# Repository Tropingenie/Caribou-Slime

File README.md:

SlimeVR PCB using ESP32-C3 and BMI 270
## Methodology
This design is intended to be assembled either completely by hand, or with some PCBA and finished by hand. Component selection is built around this, prioritizing larger form factor SMT components where possible, to ensure compatibility with and minimizing cost of the PCBA, while maintaining relatively simple assembly when done by hand.
## BOM
|    Component    |            Choice            | Amount | Cost per | Cost with Shipping |                                                                           Quick Link                                                                                                            |
|:---------------:|:----------------------------:|:------:|:--------:|:------------------:|:----------------------------------------------------------------------------------------------------------------------------------------------------------------------------------------------------------------:|
| Microcontroller | ESP32-C3 Supermini Dev Board | 12     | $2.90    | ~$41               | [AliExpress](https://www.aliexpress.com/item/1005005877531694.html), [Datasheet](https://www.tindie.com/products/adz1122/esp32-c3-development-board-esp32-supermini/), [Schematic](https://s11.ax1x.com/2023/06/26/pCUheR1.png) |
| IMU             | BMI270                       | 12     | $1.75    | ~$26               | [AliExpress](https://www.aliexpress.com/item/1005005001642144.html), [Datasheet](https://www.mouser.ca/datasheet/2/783/bst_bmi270_ds000-2529306.pdf), [Schematic](https://web.archive.org/web/20240115041534/http://cdn.kouno.xyz/pKyF5w64.pdf) |
| Batteries       | 603040 800mAh                | 10     | $3.50    | ~$31               | [AliExpress](https://www.aliexpress.com/item/1005005413532176.html)                    |
| Charging Board  | TP4056 USB-C                 | 15     | $0.329   | ~$5                | [AliExpress](https://www.aliexpress.com/item/1005005708749053.html)                    |
| Power Switches  | EG1270/MSK-12D19             | 10     | $0.085   | ~$3                | [EG Datasheet](https://www.snapeda.com/parts/EG1270/E-Switch/datasheet/), [MSK Datasheet](http://www.intechswitch.com/products/SideKnobToggleslideswitchseries/641.html), [MSK AliExpress](https://www.aliexpress.com/item/1005006241343643.html) |
| Diodes          | B5817W                       | 50     |          | ~$3                | [AliExpress](https://www.aliexpress.com/item/1005005562043696.html), [Datasheet](https://jlcpcb.com/partdetail/Hongjiacheng-B5817W/C7420328)                    |
| Resistors       | 0805 180k 5% (See schematic) | 100    |          | ~$2                | [AliExpress](https://www.aliexpress.com/item/4000996637737.html)                       |
| Resistors       | 0805 10k 5% (See schematic)  | 100    |          | ~$2                | [AliExpress](https://www.aliexpress.com/item/4000996637737.html)                       |
| Capacitors      | 0805 100nF 5% (See schematic)| 100    |          | ~$2                | [AliExpress](https://www.aliexpress.com/item/1005006285113165.html)                    |
| PCB             | Upload Gerbers               | 5      | $0.538   | ~$4                | [JLCPCB](https://jlcpcb.com/)                                                          |
## Acknowledgement
EDA files are from various sources, since there is no point in reinventing the wheel. At this stage, they are assumed to be correct, but have not been tested for accuracy.
- [BMI270](https://www.snapeda.com/parts/BMI270/Bosch%20Sensortec/view-part/) from SnapEDA
- [ESP32 C2 SuperMini](https://www.snapeda.com/parts/ESP32-C3%20SuperMini/Espressif%20Systems/view-part/) from SnapEDA
- [TP4056 Charging Board](https://www.youtube.com/watch?v=d5fERUHO1Lw) footprint copied from YouTube, schematic by observation
- [EG1270](https://www.snapeda.com/parts/EG1270/E-Switch/view-part/) from SnapEDA

Assistance from various sources was used in this project, in addition to readily available datasheets. In particular, the following people and sources have contributed to this project:
- [SlimeVR Docs](https://docs.slimevr.dev/diy/index.html) for general SlimeVR schematics
- [SlimeVR Discord](https://discord.gg/SlimeVR) for general assisance
- [KounoLab](https://store.kouno.xyz/products/bmi270-breakout-board) for additional BMI270 schematics
- @simp_360 on Discord for diode and passive component selection
- [Lupinixx](https://github.com/Lupinixx/SlimeVR-Hyperion-BMI160-PCB) and [Smeltie](https://github.com/Smeltie/Hyperion) for the Hyperion case and board outline

## License
This project is licensed under the CERN Open Hardware Licence Version 2 - Strongly Reciprocal. See [LICENSE](LICENSE) for full DEP5 formatted REUSE compliant listing of all licensing. For instructions on how to use this design, please refer to the CERN-OHL-S [user guide](cern_ohl_s_v2_user_guide.pdf).

>Copyright Pon Pon 2024.\
This source describes Open Hardware and is licensed under the CERN-OHL-S v2.
You may redistribute and modify this source and make products using it under the terms of the [CERN-OHL-S v2](https://ohwr.org/cern_ohl_s_v2.txt).\
This source is distributed WITHOUT ANY EXPRESS OR IMPLIED WARRANTY, INCLUDING OF MERCHANTABILITY, SATISFACTORY QUALITY AND FITNESS FOR A PARTICULAR PURPOSE. Please see the CERN-OHL-S v2 for applicable conditions.\
Source location: https://github.com/Tropingenie/Caribou-Slime \
As per CERN-OHL-S v2 section 4, should You produce hardware based on this source, You must where practicable maintain the Source Location visible on the silkscreen of the PCB or other products you make using this source.

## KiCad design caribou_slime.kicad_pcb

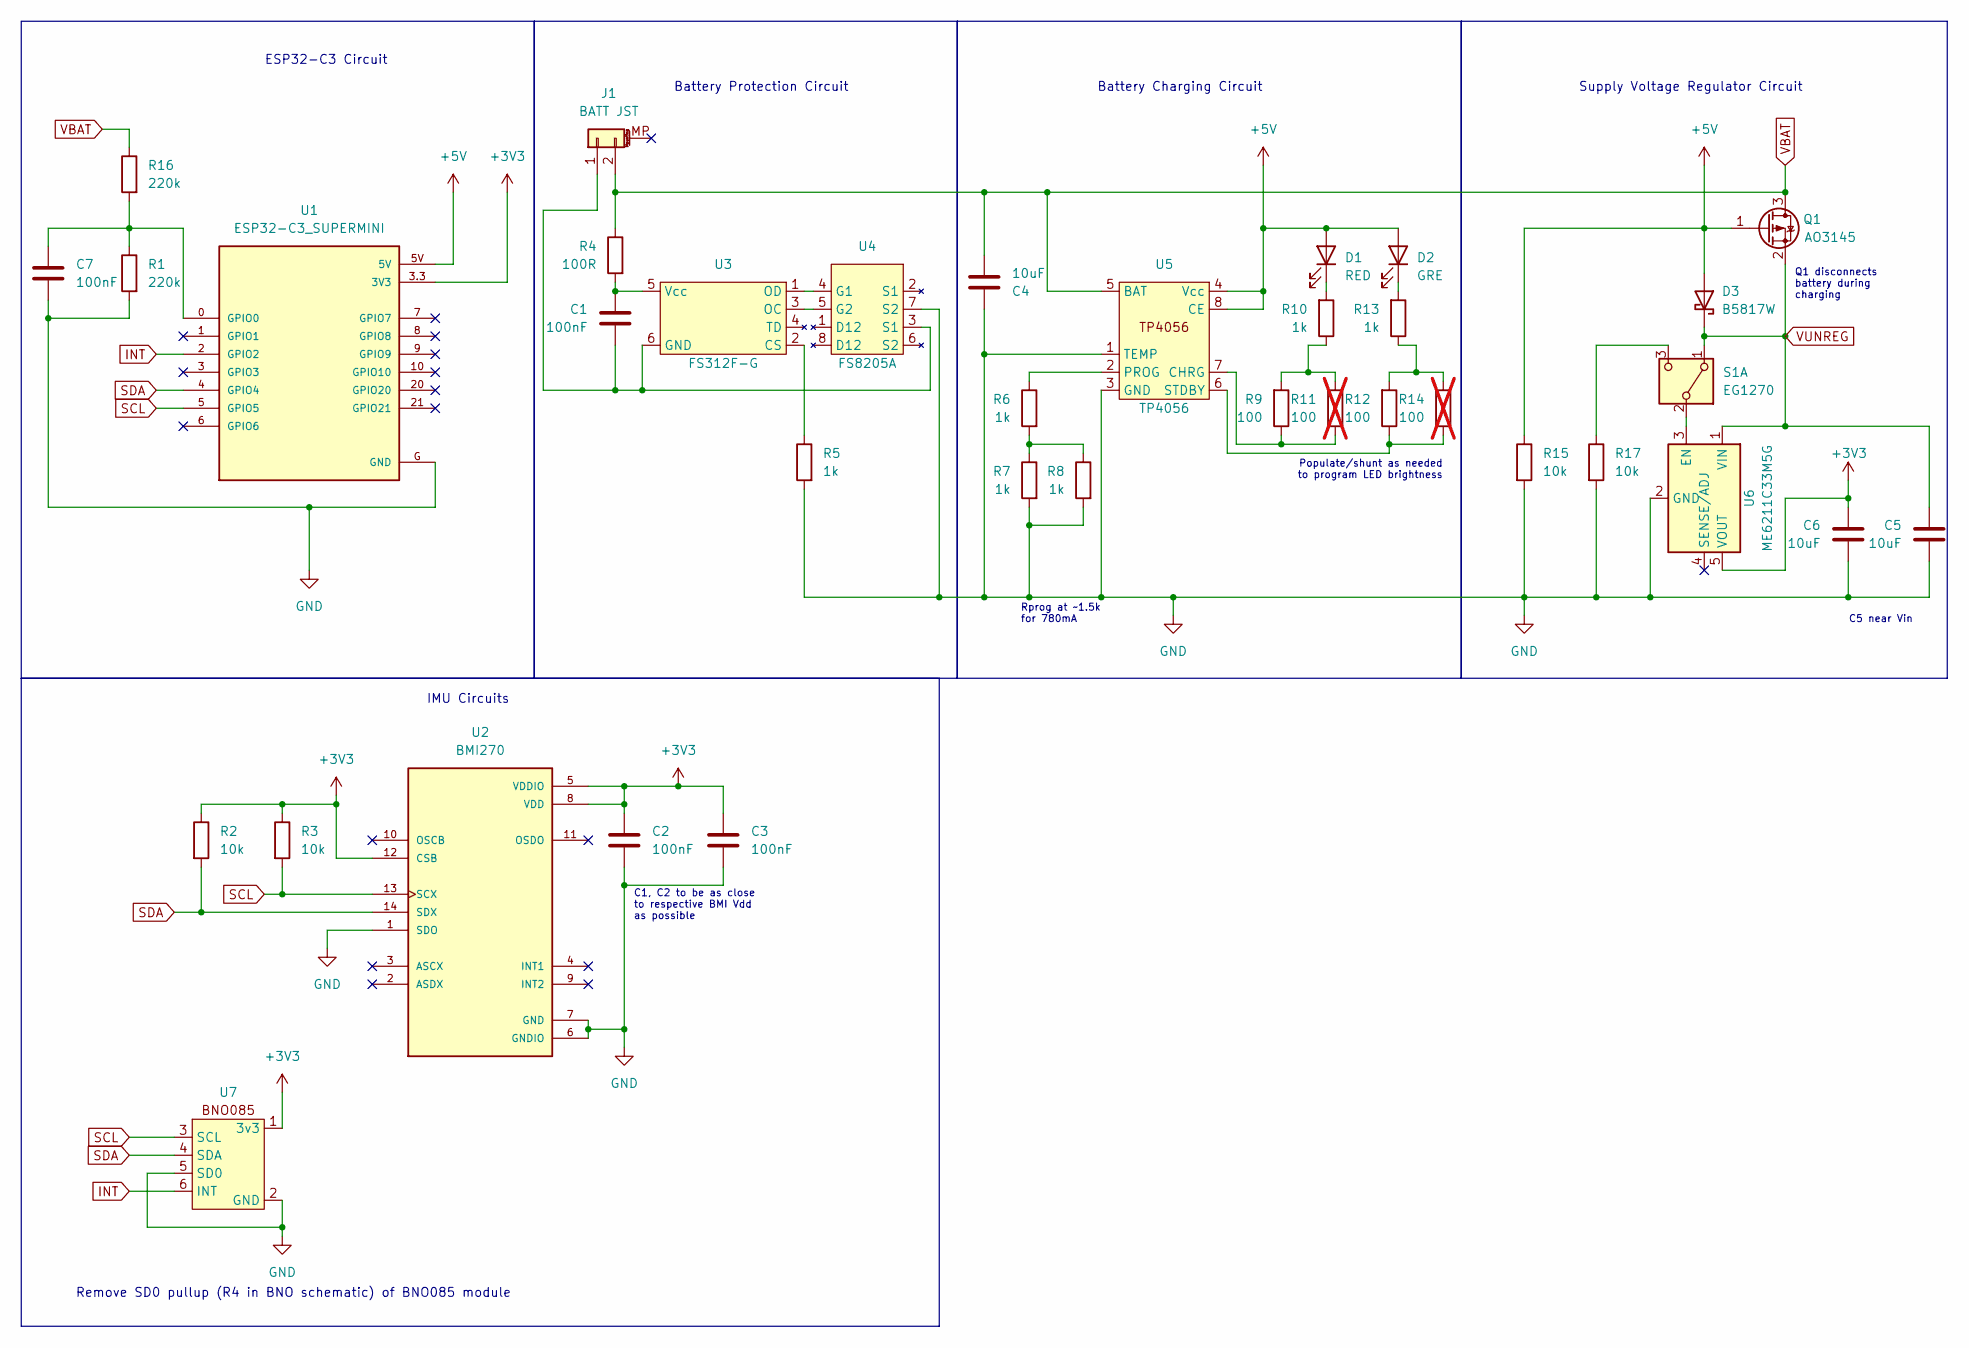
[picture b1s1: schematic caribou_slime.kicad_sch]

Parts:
C1, C2, C3, C7: 100nF; C_0805_2012Metric
C4, C5, C6: 10uF; C_0805_2012Metric
D1: RED; D_0805_2012Metric
D2: GRE; D_0805_2012Metric
D3: B5817W; D_0805_2012Metric
J1: BATT JST; JST_PH_B2B-PH-K_1x02_P2.00mm_Vertical
Q1: AO3145; SOT-23
R1, R16: 220k; R_0805_2012Metric
R2, R3, R15, R17: 10k; R_0805_2012Metric
R4: 100R; R_0805_2012Metric
R5, R6, R7, R8, R10, R13: 1k; R_0805_2012Metric
R9, R12: 100; R_0805_2012Metric
R11, R14: 100; R_0805_2012Metric; not fitted
S1: EG1270; SW_EG1270
U1: ESP32-C3_SUPERMINI; MODULE_ESP32-C3_SUPERMINI
U2: BMI270; XDCR_BMI270_HandSolder
U3: FS312F-G; TSOT-23-6
U4: FS8205A; TSSOP-8_4.4x3mm_P0.65mm
U5: TP4056; HSOP-8-1EP_3.9x4.9mm_P1.27mm_EP2.3x2.3mm
U6: ME6211C33M5G; TSOT-23-5
U7: BNO085_Module

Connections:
+3V3: C2.1, C3.1, C6.2, R2.1, R3.1, U1.3.3 (3V3), U2.5 (VDDIO), U2.8 (VDD), U2.12 (CSB), U6.5 (VOUT), U7.1 (3v3)
+5V: D1.2 (A), D2.2 (A), D3.2 (A), Q1.1 (G), R15.1, U1.5V, U5.4 (Vcc), U5.8 (CE)
GND: C2.2, C3.2, C4.1, C5.1, C6.1, C7.1, R1.2, R5.2, R7.2, R8.2, R15.2, R17.2, U1.G (GND), U2.1 (SDO), U2.6 (GNDIO), U2.7 (GND), U4.7 (S2), U5.1 (TEMP), U5.3 (GND), U6.2 (GND), U7.2 (GND), U7.5 (SD0)
INT: U1.2 (GPIO2), U7.6 (INT)
unnamed: D1.1 (K), R10.2
unnamed: D2.1 (K), R13.2
unnamed: C1.2, J1.1, U3.6 (GND), U4.3 (S1)
unnamed: R6.2, R7.1, R8.1
unnamed: R9.2, R10.1, R11.2
unnamed: R12.2, R13.1, R14.2
unnamed: S1.2 (B), U6.3 (EN)
unnamed: R17.1, S1.3 (C)
unnamed: C7.2, R1.1, R16.2, U1.0 (GPIO0)
unnamed: R5.1, U3.2 (CS)
unnamed: U3.3 (OC), U4.5 (G2)
unnamed: U3.1 (OD), U4.4 (G1)
unnamed: C1.1, R4.2, U3.5 (Vcc)
unnamed: R9.1, R11.1, U5.7 (CHRG)
unnamed: R6.1, U5.2 (PROG)
unnamed: R12.1, R14.1, U5.6 (STDBY)
SCL: R3.2, U1.5 (GPIO5), U2.13 (SCX), U7.3 (SCL)
SDA: R2.2, U1.4 (GPIO4), U2.14 (SDX), U7.4 (SDA)
VBAT: C4.2, J1.2, Q1.3 (D), R4.1, R16.1, U5.5 (BAT)
VUNREG: C5.2, D3.1 (K), Q1.2 (S), S1.1 (A), U6.1 (VIN)

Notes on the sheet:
IMU Circuits
Battery Protection Circuit
Supply Voltage Regulator Circuit
Populate/shunt as needed to program LED brightness
Remove SD0 pullup (R4 in BNO schematic) of BNO085 module
ESP32-C3 Circuit
Battery Charging Circuit
Rprog at ~1.5k for 780mA
C1, C2 to be as close to respective BMI Vdd as possible
C5 near Vin
Q1 disconnects battery during charging

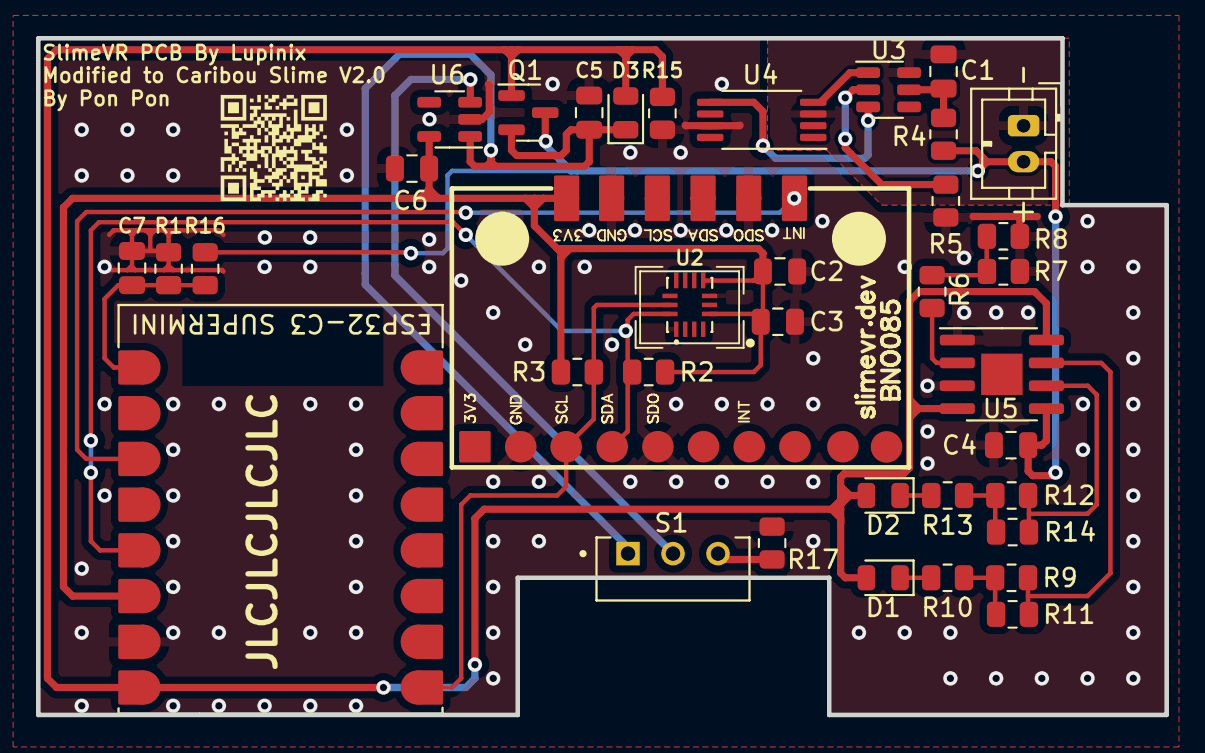
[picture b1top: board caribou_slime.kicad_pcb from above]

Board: 2 copper layers, 62.7 x 37.6 mm, 37 parts (0 on the bottom side), 24 nets.

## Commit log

2024-01-15 Initialize Project
2024-01-15 Add ESP32 dev board schematic to repo
2024-01-15 Create folder for eCAD files
2024-01-15 Add BMI270 schematic to repo
2024-01-15 Add ESP32 and BMI270 to schematic
2024-01-15 Make TP4056 charging board eCAD files
2024-01-16 Add BMI 270 circuit to schematic
2024-01-16 Add ucontroller circuit to schematic
2024-01-16 Add TP4056 circuit to schematic
2024-01-16 Add EG1270 eCAD files to repo
2024-01-16 Change generic switch for EG1270
2024-01-16 Add battery sense, correct I2C connection
2024-01-16 Add Supermini pinout diagram to repo
2024-01-16 Add label on TP4056
2024-01-16 Ground SDO on BMI270 to select correct address
2024-01-16 Revert I2C to GPIO4/5 to free 8 for LED
2024-01-17 Select B5817W diode for charge protect diodes
2024-01-17 Switch passives to 0805 SMT for JLCPCB assembly
2024-01-20 Create V1 initial PCB layout
2024-01-20 Fix caps placement, fix bat lead pitch
2024-01-20 Add SuperMini schematic to repo
2024-01-20 Update BOM
2024-01-20 Generate Gerbers for V1
2024-01-21 Finalize V1
2024-01-21 docs(git): Add changelog
2024-01-21 other(git): Add gitignores for npm files
2024-01-21 docs(pcb): Add versioning and github to silkscreen
2024-01-22 other(git) Pull in Hyperion PCB as submodule
2024-01-22 other(git) Correct submodule directory path
2024-01-22 other(git): Clean up missing submodule file path
2024-01-22 refactor(pcb): Design V1 PCB for Hyperion
2024-01-22 docs(pcb): Correct attribution and diode silkscreen
2024-01-23 docs(git): Add Hyperion attributions to README
2024-01-24 fix(pcb): Add correct JST schematic and footprint
2024-01-24 fix(pcb): Add keep-out zone around antenna
2024-01-24 chore(pcb): Add stitching vias
2024-01-24 chore(pcb): Clean up 3v3 trace
2024-01-24 docs(pcb): Update silkscreen version number
2024-01-24 chore(pcb): Remove TP4056 board
2024-01-24 chore(schematic): Remove TP4056 charging module
2024-01-24 chore(schematic): Create TP4056 IC schematic
2024-01-24 chore(schematic): Make DW01A schematic
2024-01-24 chore(schematic): Make FS8205A schematic
2024-01-24 chore(schematic): Make IP2312 schematic
2024-01-24 docs(git): Add Hayashi attribution to README
2024-01-24 chore(schematic): Prep for implementing IP2312
2024-01-24 feat(schematic): Create IP2312 charging circuit
2024-01-24 docs(git): Add attribution to Meia to README
2024-01-27 feat(schematic): Create battery auto disconnect circuit
2024-01-27 docs(schematic): Add design comments
2024-01-27 fix(schematic): Remove diode after regulator
2024-01-27 docs(git): Add Penny attribution to README
2024-01-27 docs(git): Add gorbit and nekomana attributions to README
2024-01-27 feat(schematic): Design 3v3 regulator to operate independently
2024-01-27 docs(git): Update BOM with battery components
2024-01-28 feat(schematic): Design FS312F battery protection
2024-01-28 chore(schematic): Clean up schematic
2024-01-28 fix(schematic): Correct FS8205A from datasheet
2024-01-28 docs(git): Add FS8205A to BOM
2024-01-28 chore(git): Correct casing in FS8205 datasheet filename
2024-01-28 feat(schematic): Design TP4056 charging circuit
2024-01-28 other(git): Commit spurious save
2024-01-28 chore(pcb): Cleanup after V1 and rebase
2024-01-29 fix:(schematic): Create generic LED I limiting resistor array
2024-01-29 chore(schematic): Link TP4056 datasheet and footprint
2024-01-29 chore(schematic): Renumber schematic symbol reference designators
2024-01-29 feat(pcb): Create initial V2 Hyperion layout
2024-01-29 docs(git): Add LEDs to BOM
2024-01-29 fix(pcb): Remove doglegs from capacitor routing
2024-01-29 fix(pcb): Clean up I2C lines
2024-01-29 fix(pcb): Resolve all DRC errors
2024-01-29 docs(pcb): Add QR code to repo on silk
2024-01-29 docs(git): Add holylemon89 attribution to README
2024-01-29 fix(schematic): Add voltage divider to battery sense circuit
2024-01-29 fix(schematic): Make minor corrections to regulator circuit
2024-01-29 fix(schematic): Correct battery sense voltage divider
2024-01-31 fix(pcb): Correct battery sense voltage divider
2024-01-31 chore(pcb): Create and use BMI270 Hand Solder footprint
2024-01-31 fix(pcb): Smooth 90 degree D4-K trace
2024-01-31 chore(pcb): Improve regulator aesthetics
2024-01-31 chore(pcb): Improve BMI270 aesthetics
2024-01-31 chore(pcb): Improve 270/regulator aesthetics
2024-02-01 chore(pcb): Improve SuperMini aesthetics
2024-02-01 chore(pcb): Improve TP4056 aesthetics
2024-02-01 fix(pcb): Correct malformed trace in regulator circuit
2024-02-01 fix(pcb): Rework TP4056 pin 3 to properly ground
2024-02-01 chore(pcb): Improve battery protect aesthetics
2024-02-01 chore(pcb): Resolve DRC errors mainly by reworking regulator
2024-02-01 docs(misc): Create BOM spreadsheet for cost calculation
2024-02-02 fix(pcb): Add castellated pads to SuperMini footprint
2024-02-02 other(git): Sync project file
2024-02-02 feat(pcb): Set up proper 3D models of PCB
2024-02-03 fix(schematic): Move S1A to enable pin of regulator
2024-02-03 fix(pcb): Move S1A to enable pin of regulator
2024-02-03 chore(pcb): Update ground stitching
2024-02-03 chore(pcb): Remove DNP components from 3D model
2024-02-04 fix(schematic): Add 2:1 divider to bat sense
2024-02-04 chore(pcb): Clear PCB for rework
2024-02-04 docs(pcb): Prep silk screen for V1.1 Hyperion layout
2024-02-04 fix(schematic): Switch C1 footprint to 0805
2024-02-04 chore(pcb): Run S1 trace
2024-02-04 feat(pcb): Design V1.1 PCB layout
2024-02-04 docs(pcb): Fix silkscreen text
2024-02-05 chore(pcb): Clean up SCL trace, stiching vias
2024-02-05 fix(schematic): Correct GPIO0 connection to voltage divider
2024-02-05 chore(git): Update gitignore with Outputs folder
2024-02-05 fix(pcb): Update GPIO0 connection to voltage divider
2024-02-05 docs(git): Update changelog for v1.1 release
2024-02-06 fix(schematic): Add pulldown to regulator EN pin
2024-02-06 fix(pcb): Update PCB to match latest schematic
2024-02-08 refactor(schematic): Rework S1A to disconnect pulldown when reg en high
2024-02-08 chore(schematic): Remove spurious D3 (SuperMini reg has not been usable since e673114ec8c1bcd027ae6eac0da885c535fbe167 )
2024-02-08 chore(schematic): Clean up regulator schematic
2024-02-08 fix(pcb): Update PCB with new S1A traces
2024-02-08 fix(schematic): Fix shorted battery nets
2024-02-08 fix(pcb): Fix shorted battery nets
2024-02-08 other(git): Commit kicad_pro
2024-02-08 docs(git): Add licensing information
2024-02-08 docs(git): Add CERN-OHL-S-V2 user guide to repo
2024-02-11 docs(git): Update links in README
2024-02-13 refactor(pcb): Increase TP4056 trace widths to 18 mil
2024-02-15 docs(pcb): Restore U2 label on silk
2024-02-23 chore(pcb): Create BNO085 module footprint
2024-02-23 chore(schematic): Create BNO085 symbol
2024-02-23 feat(schematic): Add BNO085 as alternate IMU
2024-02-23 chore(pcb): Update SuperMini footprint to SMT only
2024-02-23 feat(pcb): Add BNO085 module
2024-02-24 chore(pcb): Run traces for battery protection
2024-02-24 chore(pcb): Run reg traces
2024-02-25 chore(pcb): IMU traces
2024-02-25 chore(pcb): Run battery charging traces
2024-02-25 chore(pcb): Finishing touches (DRC, stitching, silk)
2024-02-25 chore(pcb): Add SuperMini and 270 3D models
2024-03-18 chore(pcb): Add BMI270 model
2024-03-19 feature(schematic): Replace LDO with buck-boost regulator
2024-03-19 feat(schematic): Swap TP4056 for LTC4054 charging IC
2024-03-21 docs(schematic): Adjust notes and labels
2024-11-28 chore(schematic): Switch to 8.5x11 paper
